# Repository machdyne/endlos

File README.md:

# Endlos Computer

Endlos is a 1-layer FPGA computer designed by Lone Dynamics Corporation.

This repo contains schematics, PCB layouts, pinouts, example gateware and documentation.

Find more information on the [Endlos product page](https://machdyne.com/product/endlos-computer/).

## Blinky 

Building the blinky example requires [Yosys](https://github.com/YosysHQ/yosys), [nextpnr-ice40](https://github.com/YosysHQ/nextpnr) and [IceStorm](https://github.com/YosysHQ/icestorm).

## Pinouts

### PMOD Socket (left, pins top-to-bottom)

| Pin | Signal | Description |
| ----| ------ | ----------- |
| 1 | PMOD\_A1 | GPIO |
| 2 | PMOD\_A2 | GPIO |
| 3 | PMOD\_A3 | GPIO |
| 4 | PMOD\_A4 | GPIO |
| 5 | GND | Ground |
| 6 | 3V3 | Power |

### MMOD Socket (bottom, pins left-to-right)

| Pin | Signal | Description |
| --- | ------ | ----------- |
| 1 | CSPI\_SS | GPIO |
| 2 | CSPI\_SO | GPIO |
| 3 | CSPI\_SI | GPIO |
| 4 | CSPI\_SCK | GPIO |
| 5 | GND | Ground |
| 6 | 3V3 | Power |

### Audio/Video Jack

| Pin | Description |
| --- | ----------- |
| T | Mono Audio |
| R1 | Mono Audio |
| R2 | Video |
| S | Ground |

## Board Revisions

| Revision | Notes |
| -------- | ----- |
| V0 | Initial version |

Note #1: All of the functionality hasn't been tested yet, only configuration from MMOD and blinky on an LED PMOD.

Note #2: There should probably be a 10K pull-up on RAM\_SS, but configuration appears to work without it.

Note #3: Kapton tape is recommended under front of the USB-B connector.

## License

The contents of this repo are released under the [Lone Dynamics Open License](LICENSE.md).

Note: You can use these designs for commercial purposes but we ask that instead of producing exact clones, that you either replace our trademarks and logos with your own or add your own next to ours.

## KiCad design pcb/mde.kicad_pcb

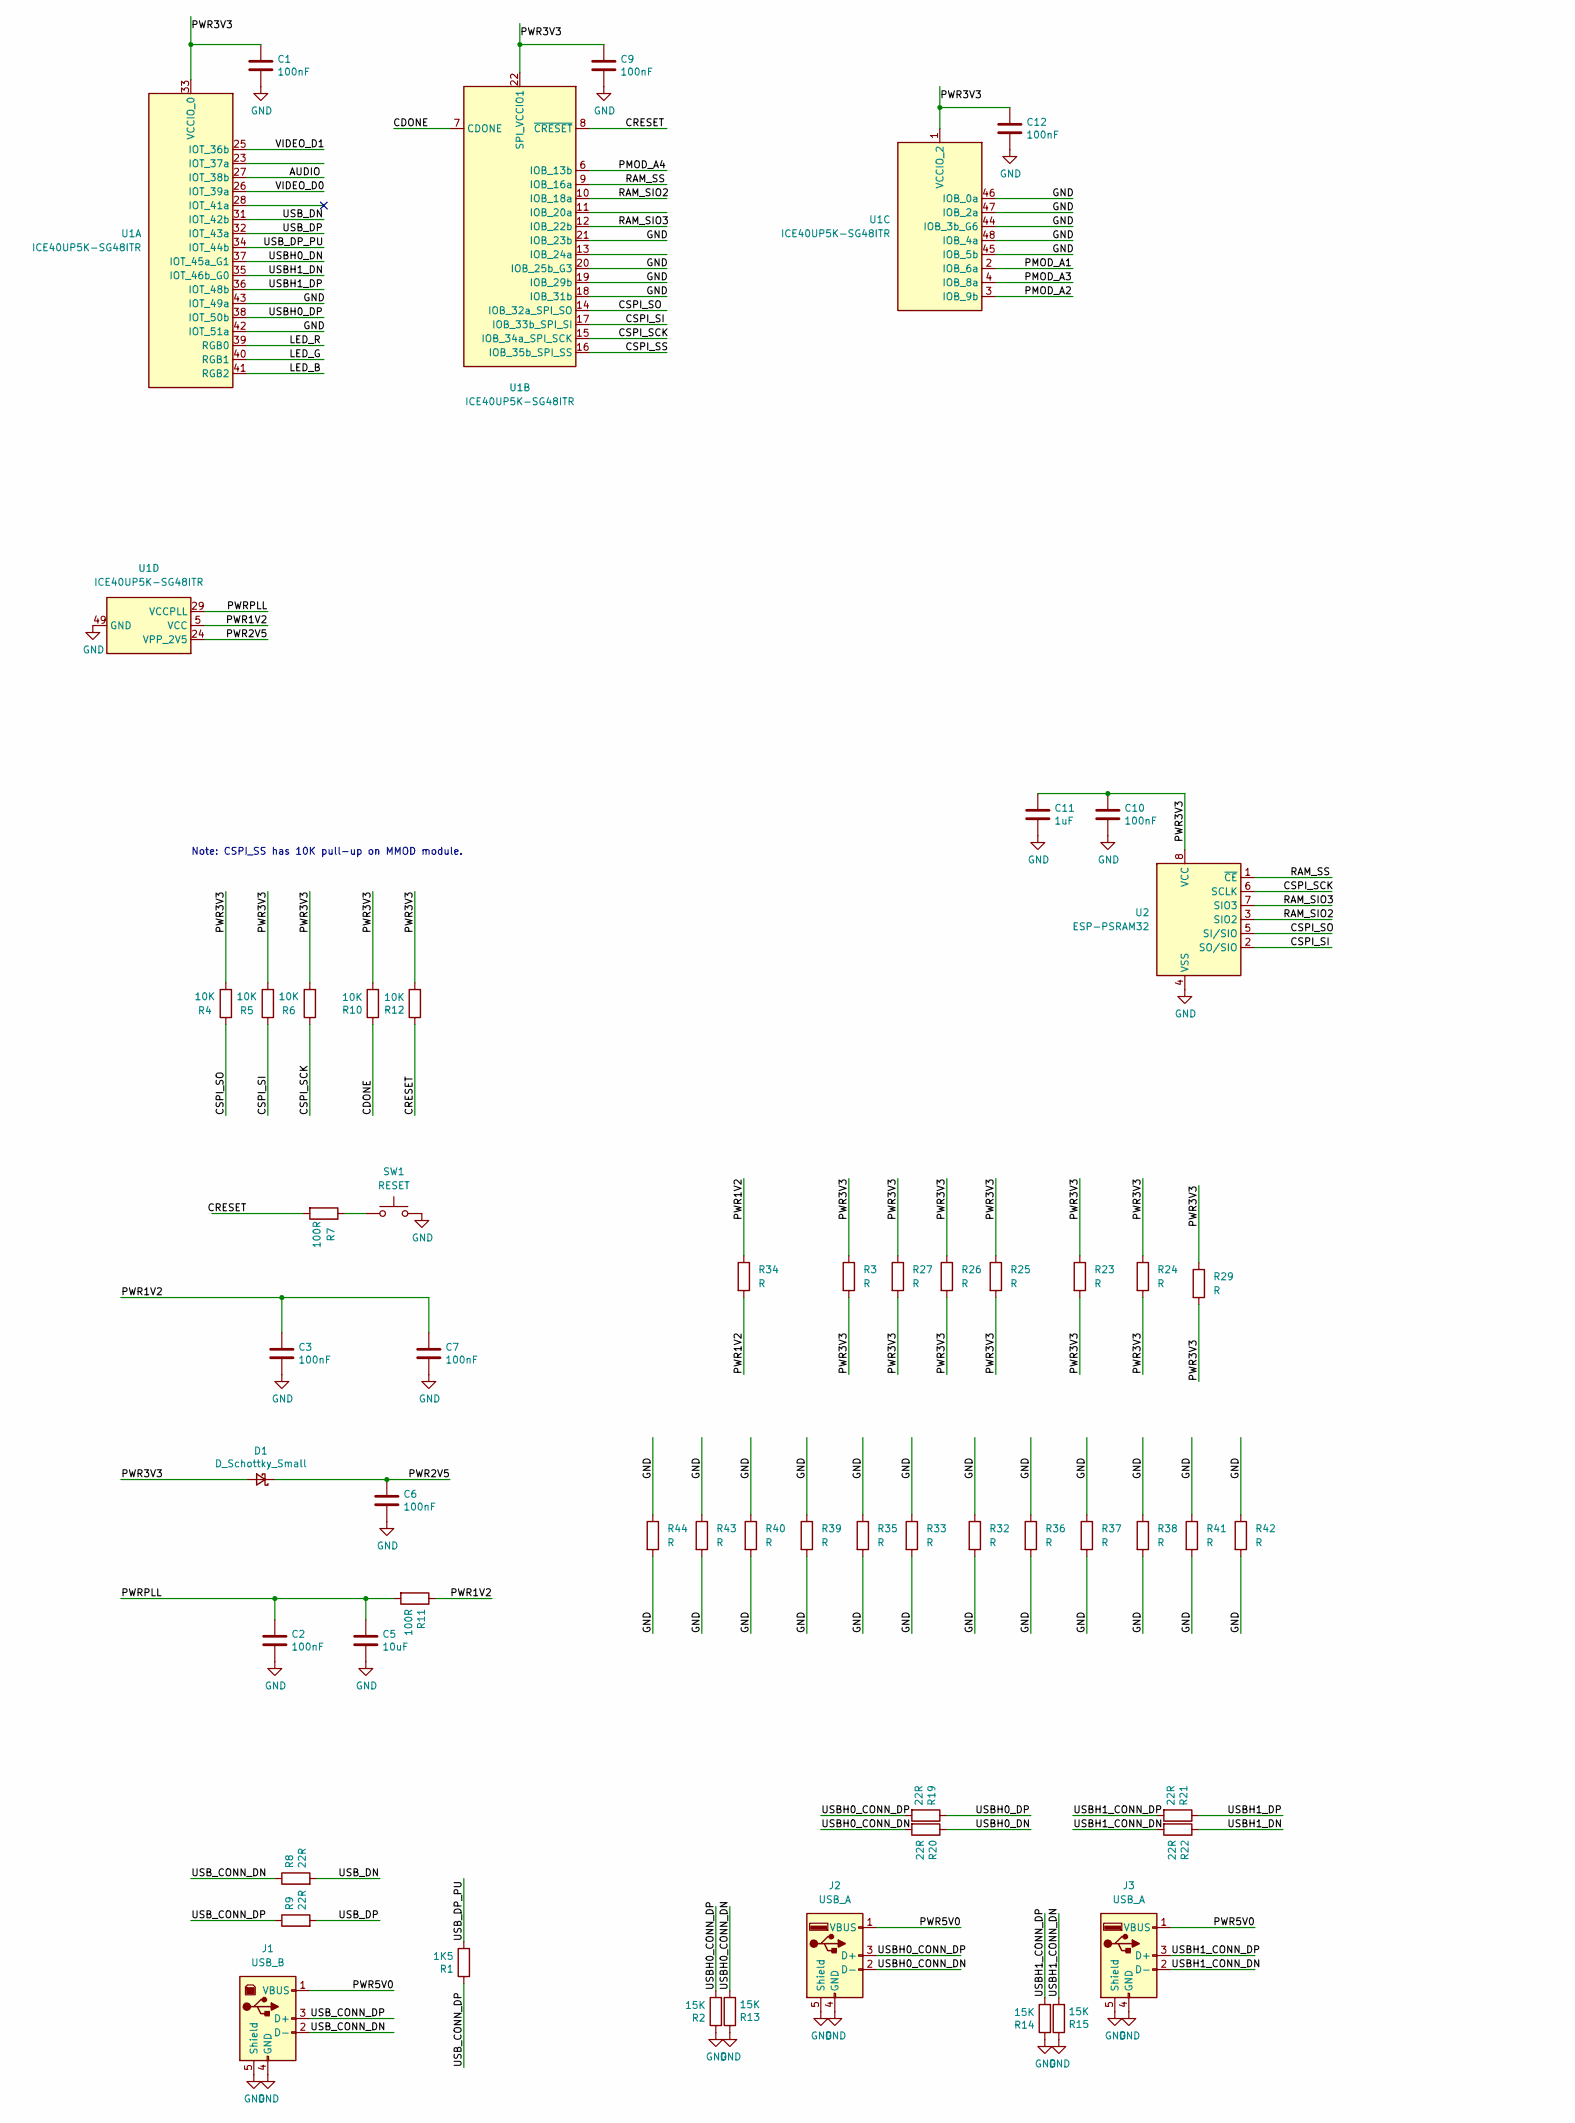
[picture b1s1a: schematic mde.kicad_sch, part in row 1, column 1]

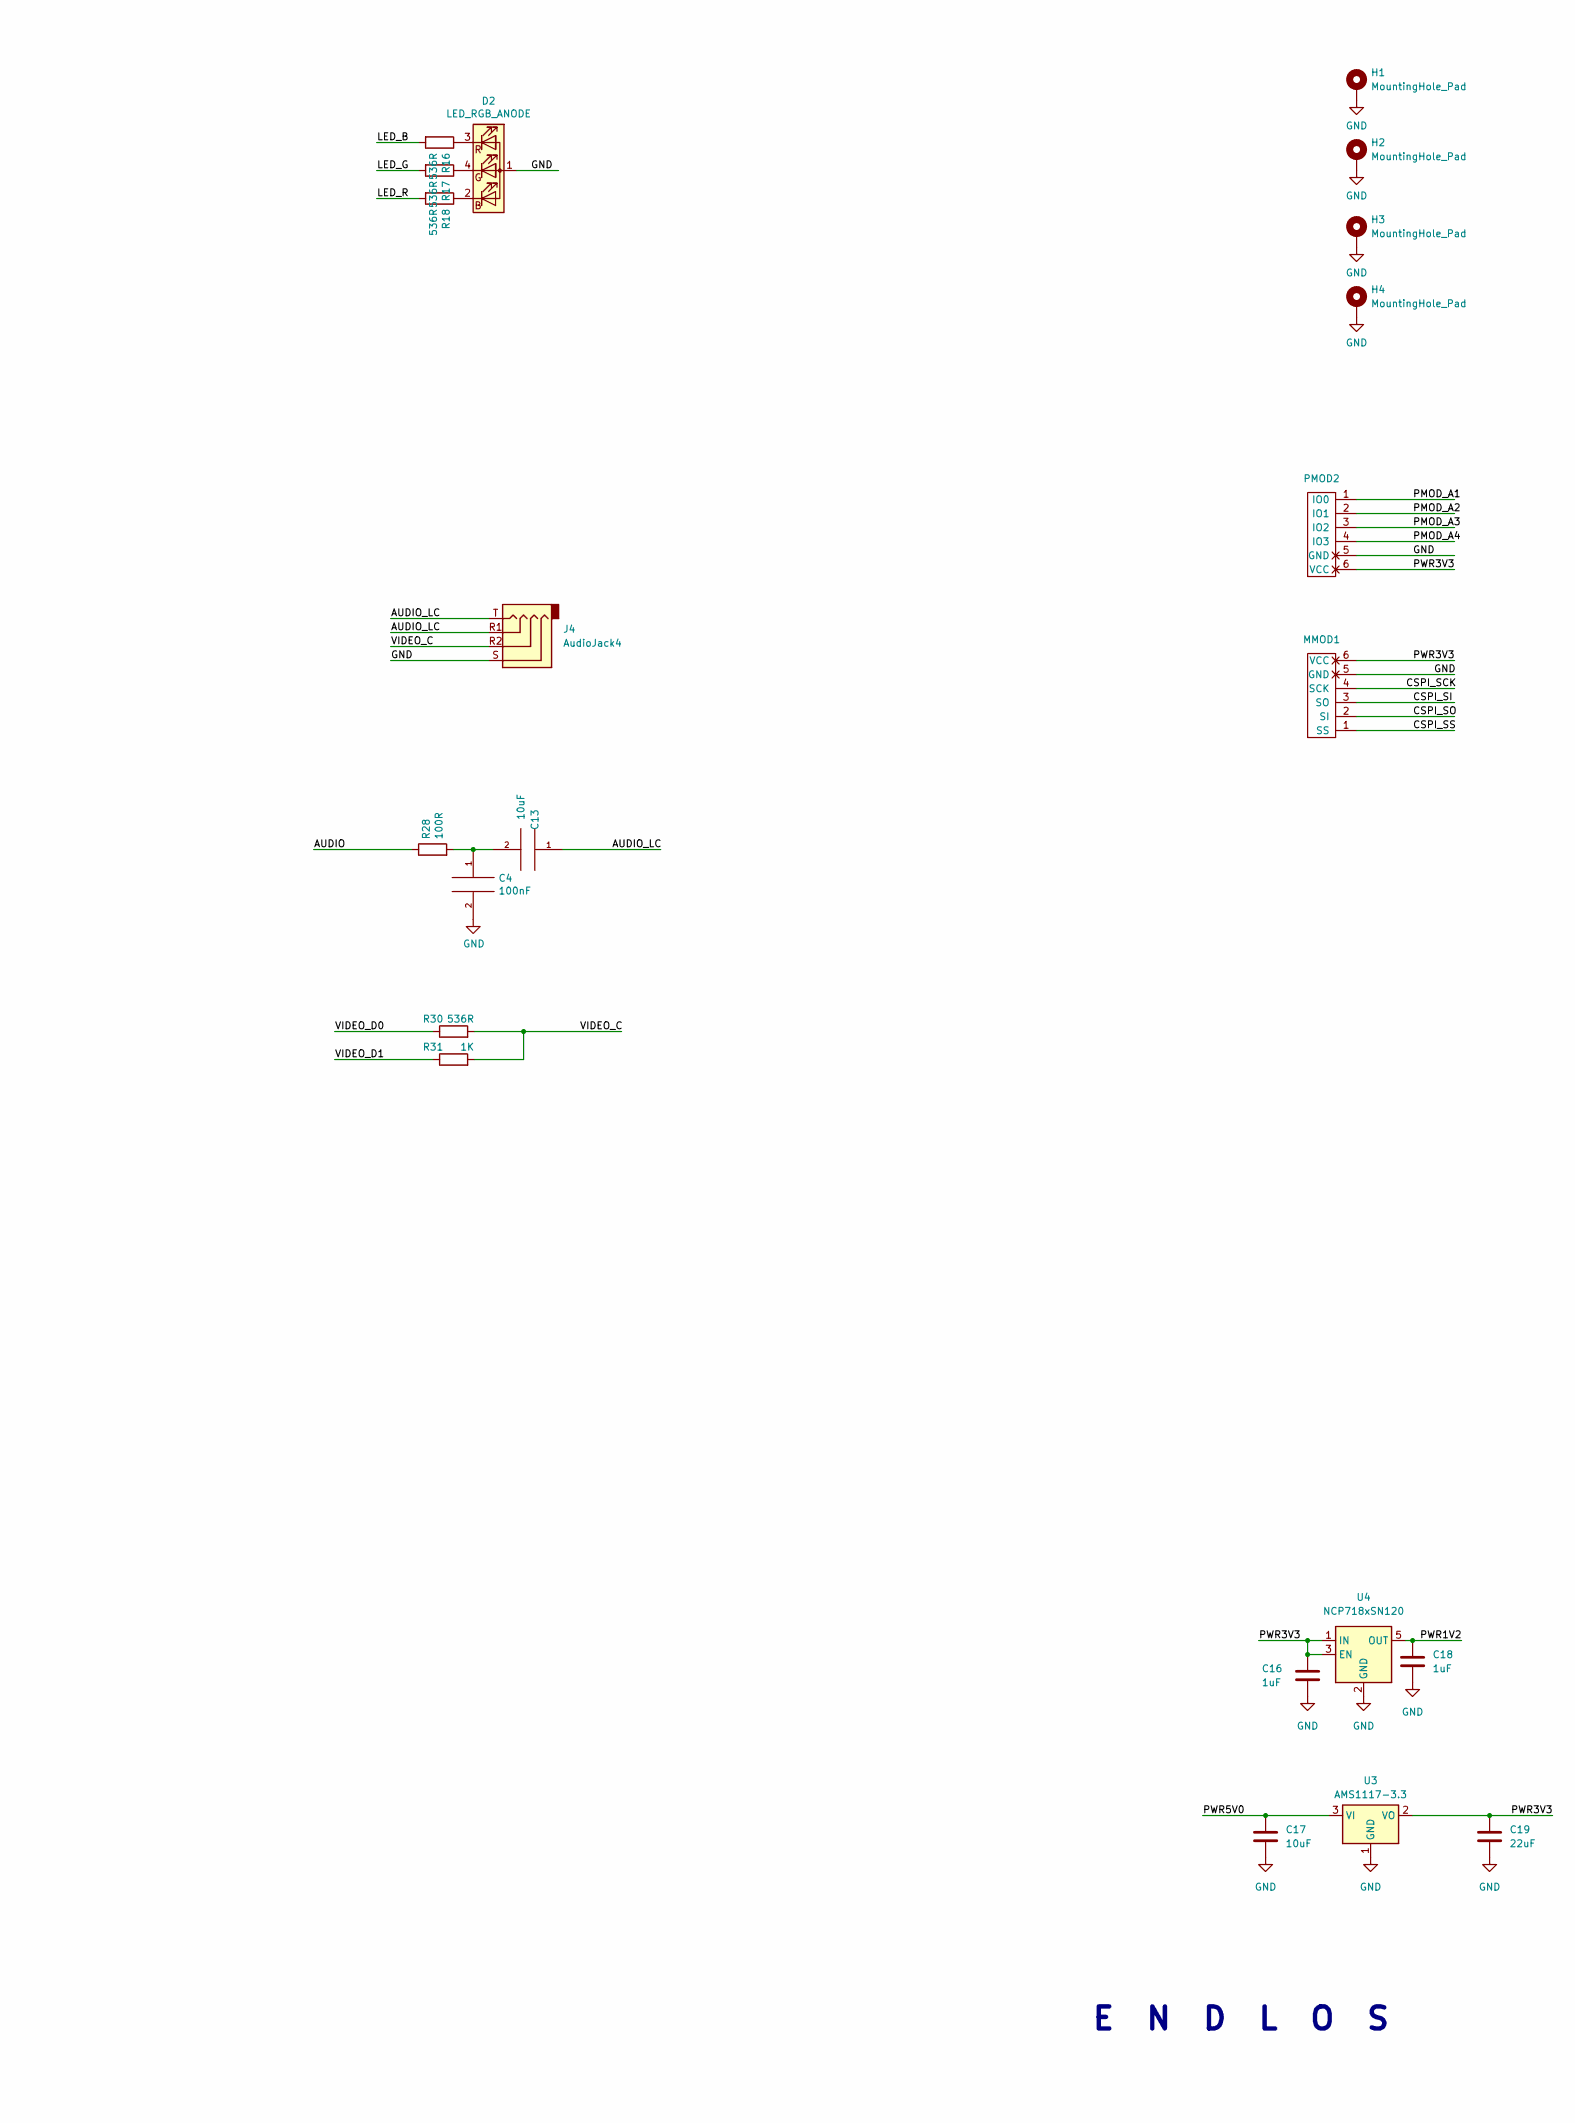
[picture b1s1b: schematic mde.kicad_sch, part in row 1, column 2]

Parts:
C1, C2, C3, C4, C6, C7, C9, C10, C12: 100nF; C_0603_1608Metric
C5, C13, C17: 10uF; C_0603_1608Metric
C11, C16, C18: 1uF; C_0603_1608Metric
C19: 22uF; C_0603_1608Metric
D1: D_Schottky_Small; D_0603_1608Metric
D2: LED_RGB_ANODE; LED_RGB_0606_CHANZON
H1, H2, H3, H4: MountingHole_Pad; MountingHole_3.2mm_M3_ISO7380_Pad_TopOnly
J1: USB_B; SAMTEC_USB-B-S-X-X-SM-TR
J2, J3: USB_A; SAMTEC_USB-A-S-X-X-SM2
J4: AudioJack4; Jack_3.5mm_PJ320D_Horizontal
MMOD1: MMOD_Host_Socket; PinSocket_1x06_P2.54mm_Vertical_SMD_Pin1Left
PMOD2: PMOD-Host-x1-GPIO; PinSocket_1x06_P2.54mm_Vertical_SMD_Pin1Left
R1: 1K5; R_0603_1608Metric
R2, R13, R14, R15: 15K; R_0603_1608Metric
R3, R25, R26, R27, R33, R35, R39, R40, R43, R44: R; R_0603_1608Metric
R4, R5, R6, R10, R12: 10K; R_0603_1608Metric
R7, R11, R28: 100R; R_0603_1608Metric
R8, R9, R19, R20, R21, R22: 22R; R_0603_1608Metric
R16, R17, R18, R30: 536R; R_0603_1608Metric
R23, R24, R29, R32, R34, R36, R37, R38, R41, R42: R; R_1206_3216Metric
R31: 1K; R_0603_1608Metric
SW1: RESET; Button_2P_3x4mm
U1: ICE40UP5K-SG48ITR; QFN-48-1EP_7x7mm_P0.5mm_EP5.6x5.6mm
U2: ESP-PSRAM32; SOIC-8_3.9x4.9mm_P1.27mm
U3: AMS1117-3.3; SOT-223-3_TabPin2
U4: NCP718xSN120; SOT-23-5

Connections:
/AUDIO: R28.1, U1.27 (IOT_38b)
/AUDIO_LC: C13.1, J4.R1, J4.T
/CDONE: R10.1, U1.7 (CDONE)
/CRESET: R7.2, R12.1, U1.8 (~CRESET)
/CSPI_SCK: MMOD1.4 (SCK), R6.1, U1.15 (IOB_34a_SPI_SCK), U2.6 (SCLK)
/CSPI_SI: MMOD1.3 (SO), R5.1, U1.17 (IOB_33b_SPI_SI), U2.2 (SO/SIO)
/CSPI_SO: MMOD1.2 (SI), R4.1, U1.14 (IOB_32a_SPI_SO), U2.5 (SI/SIO)
/CSPI_SS: MMOD1.1 (SS), U1.16 (IOB_35b_SPI_SS)
/LED_B: R16.2, U1.41 (RGB2)
/LED_G: R17.2, U1.40 (RGB1)
/LED_R: R18.2, U1.39 (RGB0)
/PMOD_A1: PMOD2.1 (IO0), U1.2 (IOB_6a)
/PMOD_A2: PMOD2.2 (IO1), U1.3 (IOB_9b)
/PMOD_A3: PMOD2.3 (IO2), U1.4 (IOB_8a)
/PMOD_A4: PMOD2.4 (IO3), U1.6 (IOB_13b)
/PWR1V2: C3.1, C7.1, C18.1, R11.1, R34.1, R34.2, U1.5 (VCC), U1.30 (VCC), U4.5 (OUT)
/PWR2V5: C6.1, D1.1 (K), U1.24 (VPP_2V5)
/PWR3V3: C1.1, C9.1, C10.1, C11.1, C12.1, C16.1, C19.1, D1.2 (A), MMOD1.6 (VCC), PMOD2.6 (VCC), R3.1, R3.2, R4.2, R5.2, R6.2, R10.2, R12.2, R23.1, R23.2, R24.1, R24.2, R25.1, R25.2, R26.1, R26.2, R27.1, R27.2, R29.1, R29.2, U1.1 (VCCIO_2), U1.22 (SPI_VCCIO1), U1.33 (VCCIO_0), U2.8 (VCC), U3.2 (VO), U4.1 (IN), U4.3 (EN)
/PWR5V0: C17.1, J1.1 (VBUS), J2.1 (VBUS), J3.1 (VBUS), U3.3 (VI)
/PWRPLL: C2.1, C5.1, R11.2, U1.29 (VCCPLL)
/RAM_SIO2: U1.10 (IOB_18a), U2.3 (SIO2)
/RAM_SIO3: U1.12 (IOB_22b), U2.7 (SIO3)
/RAM_SS: U1.9 (IOB_16a), U2.1 (~CE)
/USBH0_CONN_DN: J2.2 (D-), R13.2, R20.2
/USBH0_CONN_DP: J2.3 (D+), R2.2, R19.2
/USBH0_DN: R20.1, U1.37 (IOT_45a_G1)
/USBH0_DP: R19.1, U1.38 (IOT_50b)
/USBH1_CONN_DN: J3.2 (D-), R15.2, R22.2
/USBH1_CONN_DP: J3.3 (D+), R14.2, R21.2
/USBH1_DN: R22.1, U1.35 (IOT_46b_G0)
/USBH1_DP: R21.1, U1.36 (IOT_48b)
/USB_CONN_DN: J1.2 (D-), R8.1
/USB_CONN_DP: J1.3 (D+), R1.1, R9.1
/USB_DN: R8.2, U1.31 (IOT_42b)
/USB_DP: R9.2, U1.32 (IOT_43a)
/USB_DP_PU: R1.2, U1.34 (IOT_44b)
/VIDEO_C: J4.R2, R30.2, R31.2
/VIDEO_D0: R30.1, U1.26 (IOT_39a)
/VIDEO_D1: R31.1, U1.25 (IOT_36b)
GND: C1.2, C2.2, C3.2, C4.2, C5.2, C6.2, C7.2, C9.2, C10.2, C11.2, C12.2, C16.2, C17.2, C18.2, C19.2, D2.1 (A), H1.1, H2.1, H3.1, H4.1, J1.4 (GND), J1.5 (Shield), J2.4 (GND), J2.5 (Shield), J3.4 (GND), J3.5 (Shield), J4.S, MMOD1.5 (GND), PMOD2.5 (GND), R2.1, R13.1, R14.1, R15.1, R32.1, R32.2, R33.1, R33.2, R35.1, R35.2, R36.1, R36.2, R37.1, R37.2, R38.1, R38.2, R39.1, R39.2, R40.1, R40.2, R41.1, R41.2, R42.1, R42.2, R43.1, R43.2, R44.1, R44.2, SW1.2, U1.18 (IOB_31b), U1.19 (IOB_29b), U1.20 (IOB_25b_G3), U1.21 (IOB_23b), U1.42 (IOT_51a), U1.43 (IOT_49a), U1.44 (IOB_3b_G6), U1.45 (IOB_5b), U1.46 (IOB_0a), U1.47 (IOB_2a), U1.48 (IOB_4a), U1.49 (GND), U2.4 (VSS), U3.1 (GND), U4.2 (GND)
unnamed: C4.1, C13.2, R28.2
unnamed: D2.2 (BK), R18.1
unnamed: D2.4 (GK), R17.1
unnamed: D2.3 (RK), R16.1
unnamed: R7.1, SW1.1

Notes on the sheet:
E N D L O S
Note: CSPI_SS has 10K pull-up on MMOD module.

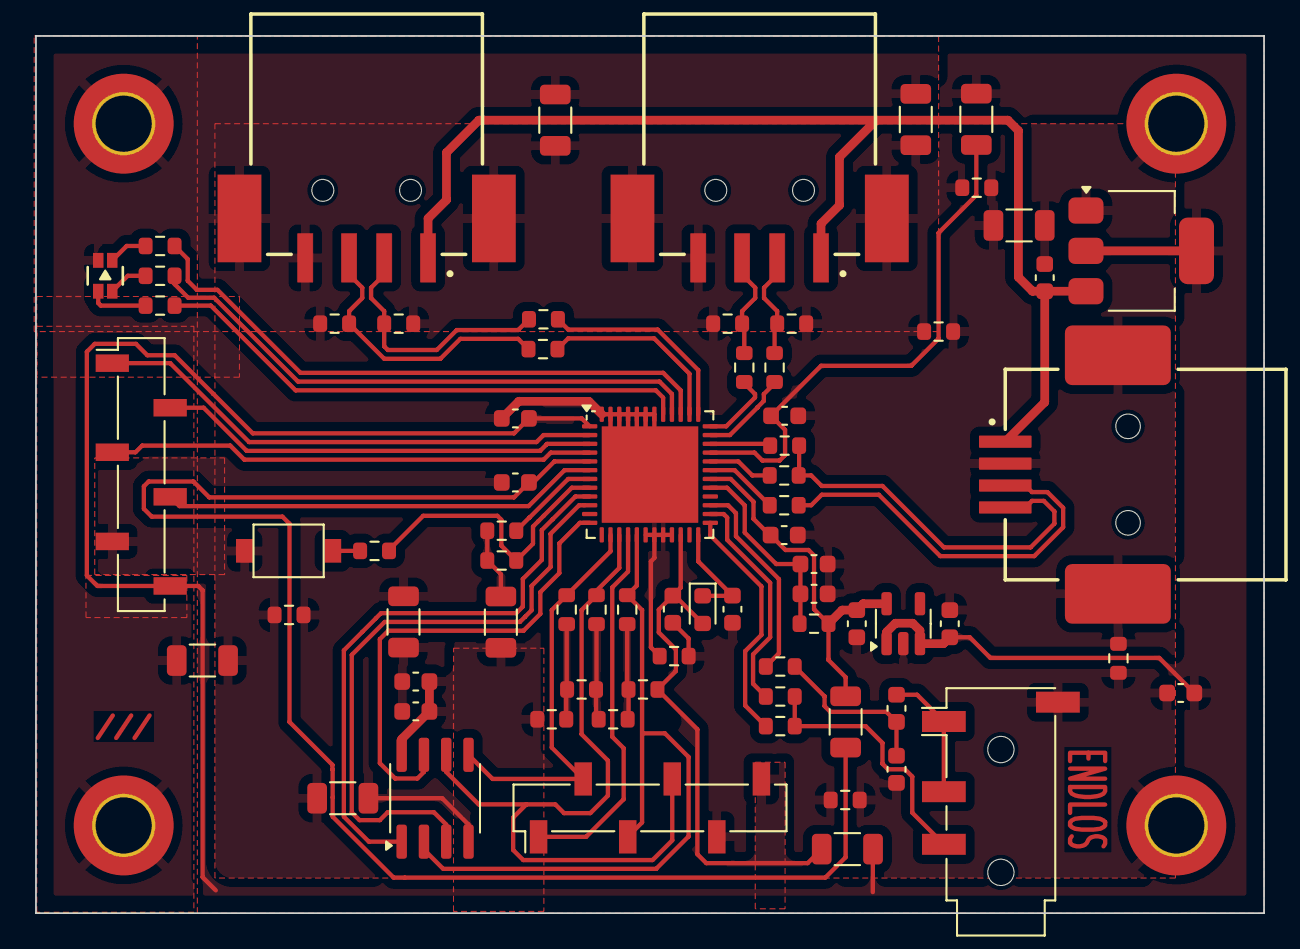
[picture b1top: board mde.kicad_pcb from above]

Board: 2 copper layers, 70.0 x 50.0 mm, 77 parts (0 on the bottom side), 45 nets.

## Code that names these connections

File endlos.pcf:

# Endlos V0
# ---------

# RGB LED
set_io LED_R	40
set_io LED_G	41
set_io LED_B	39

# PMOD_A
set_io PMOD_A1		2
set_io PMOD_A2		3
set_io PMOD_A3		4
set_io PMOD_A4		6

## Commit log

2024-09-12 rename image
